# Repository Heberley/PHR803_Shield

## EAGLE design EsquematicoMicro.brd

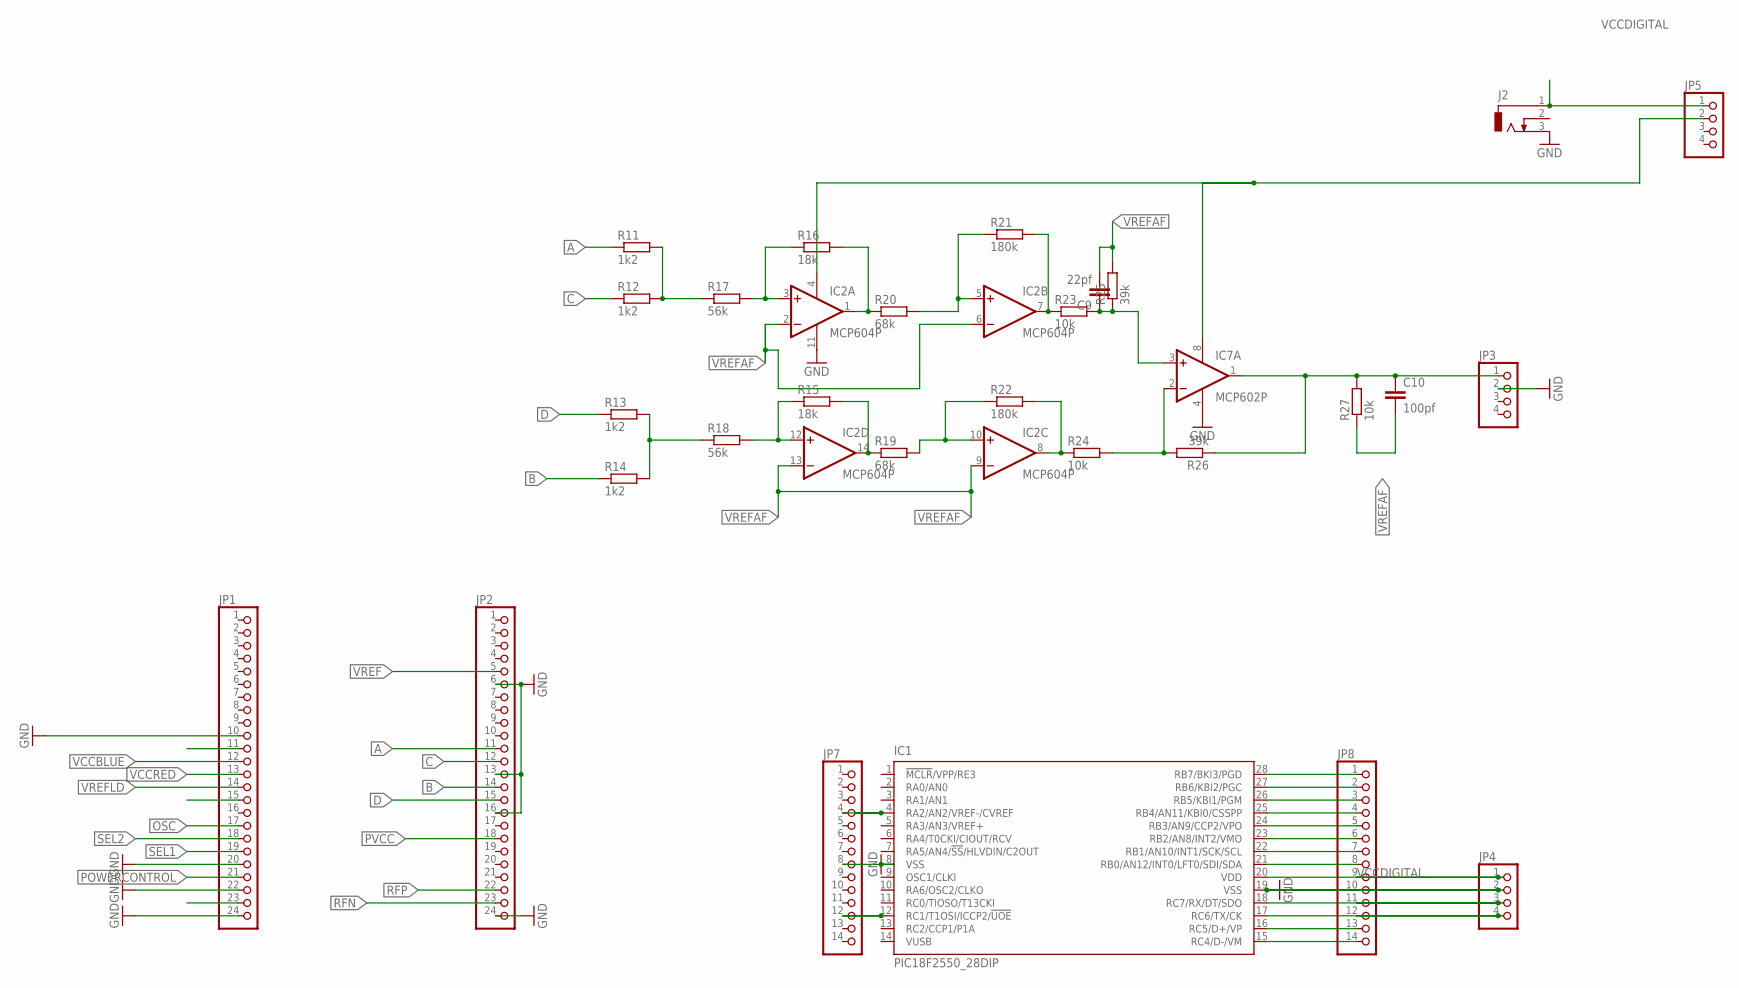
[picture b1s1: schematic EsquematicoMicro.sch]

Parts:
C9: 22pf; C025-025X050
C10: 100pf; C025-025X050
IC1: PIC18F2550_28DIP; DIL28-3
IC2: MCP604P; DIL14
IC7: MCP602P; DIL08
J2: DCJ0303
JP1, JP2: PINHD-1X24; 1X24
JP3, JP4, JP5: PINHD-1X4; 1X04
JP7, JP8: PINHD-1X14; 1X14
R11, R12, R13, R14: 1k2; 0204/5
R15, R16: 18k; 0204/5
R17, R18: 56k; 0204/5
R19, R20: 68k; 0204/5
R21, R22: 180k; 0204/5
R23, R24, R27: 10k; 0204/5
R25, R26: 39k; 0204/5

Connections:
A: JP2.11, R11.1
B: JP2.14, R14.1
C: JP2.12, R12.1
D: JP2.15, R13.1
GND: IC1.8 (VSS), IC1.19 (VSS), IC2.11 (V-), IC7.4 (V-), J2.3, JP1.10, JP1.20, JP1.22, JP1.24, JP2.6, JP2.13, JP2.16, JP2.24, JP3.2, JP4.2, JP7.8, JP8.10
LASERMICRO: IC1.4 (RA2/AN2/VREF-/CVREF), JP7.4
unnamed: IC1.18 (RC7/RX/DT/SDO), JP4.3, JP8.11
unnamed: IC1.17 (RC6/TX/CK), JP4.4, JP8.12
unnamed: IC1.28 (RB7/BKI3/PGD), JP8.1
unnamed: IC1.27 (RB6/KBI2/PGC), JP8.2
unnamed: IC1.25 (RB4/AN11/KBI0/CSSPP), JP8.4
unnamed: IC1.23 (RB2/AN8/INT2/VMO), JP8.6
unnamed: IC1.22 (RB1/AN10/INT1/SCK/SCL), JP8.7
unnamed: IC1.21 (RB0/AN12/INT0/LFT0/SDI/SDA), JP8.8
unnamed: IC1.16 (RC5/D+/VP), JP8.13
unnamed: IC1.15 (RC4/D-/VM), JP8.14
unnamed: IC1.26 (RB5/KBI1/PGM), JP8.3
unnamed: R11.2, R12.2, R17.1
unnamed: R13.2, R14.2, R18.1
unnamed: IC2.3 (+IN), R16.1, R17.2
unnamed: IC2.12 (+IN), R15.1, R18.2
unnamed: IC2.1 (OUT), R16.2, R20.1
unnamed: IC2.14 (OUT), R15.2, R19.1
unnamed: IC2.10 (+IN), R19.2, R22.1
unnamed: IC2.8 (OUT), R22.2, R24.1
unnamed: IC2.5 (+IN), R20.2, R21.1
unnamed: IC2.4 (V+), IC7.8 (V+), JP5.2
unnamed: C9.1, IC7.3 (+IN), R23.2, R25.1
unnamed: IC7.2 (-IN), R24.2, R26.2
unnamed: C10.1, IC7.1 (OUT), JP3.1, R26.1, R27.2
unnamed: IC2.7 (OUT), R21.2, R23.1
OSC: JP1.17
POWERCONTROL: JP1.21
PVCC: JP2.18
PWMTILT: IC1.24 (RB3/AN9/CCP2/VPO), JP8.5
PWMY: IC1.12 (RC1/T1OSI/ICCP2/!UOE), JP7.12
RFN: JP2.23
RFP: JP2.22
SEL1: JP1.19
SEL2: JP1.18
VCCBLUE: JP1.12
VCCDIGITAL: IC1.20 (VDD), J2.1, JP4.1, JP5.1, JP8.9
VCCRED: JP1.13
VREF: JP2.5
VREFAF: C9.2, C10.2, IC2.2 (-IN), IC2.6 (-IN), IC2.9 (-IN), IC2.13 (-IN), R25.2, R27.1
VREFLD: JP1.14

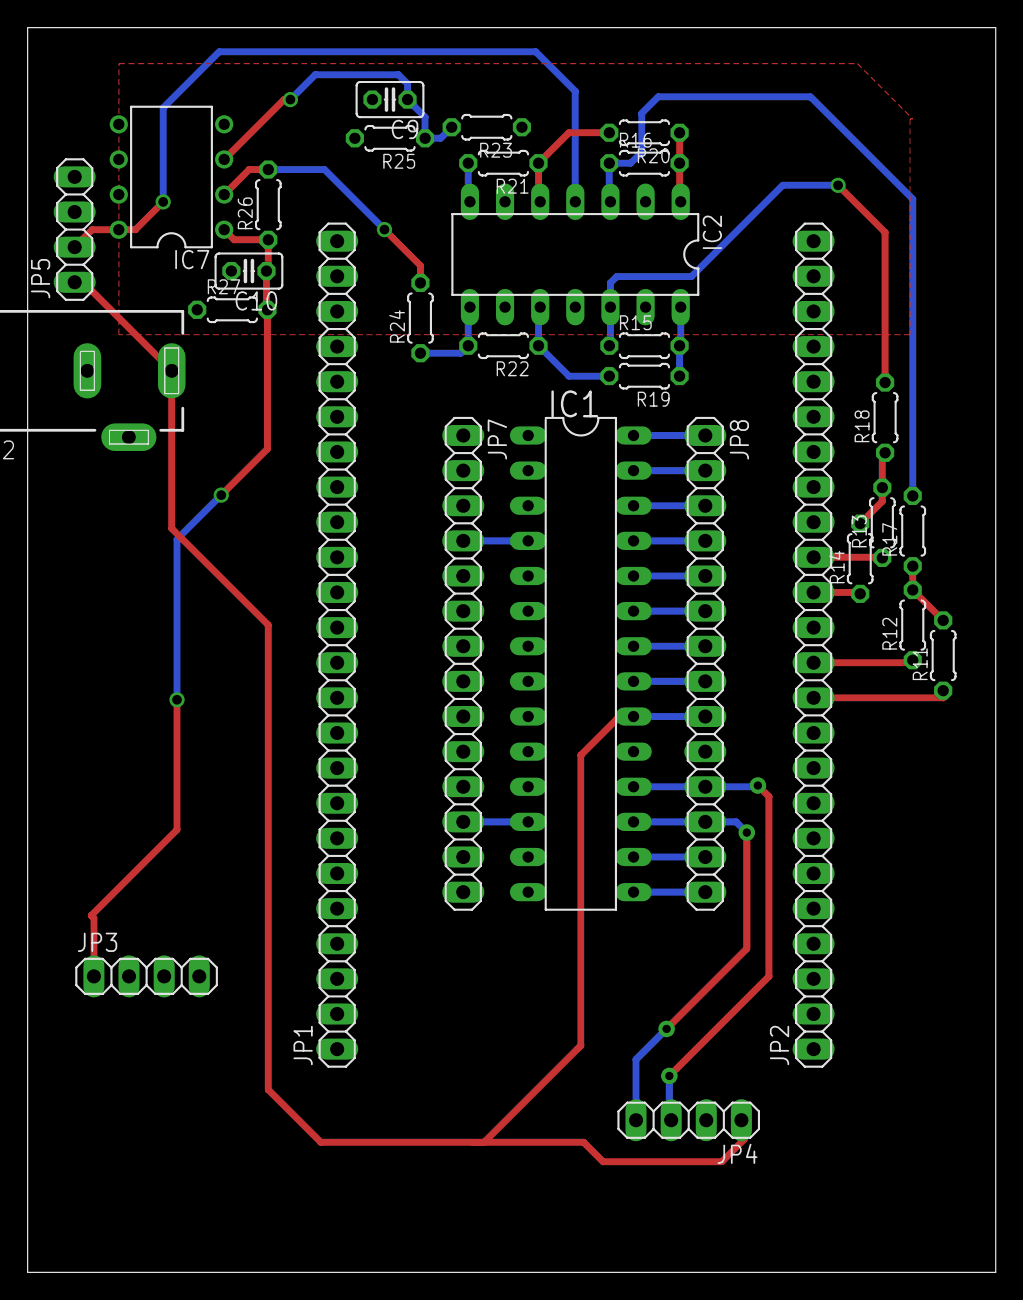
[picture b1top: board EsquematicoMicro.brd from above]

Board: 2 copper layers, 70.0 x 90.0 mm, 30 parts (0 on the bottom side), 35 nets.

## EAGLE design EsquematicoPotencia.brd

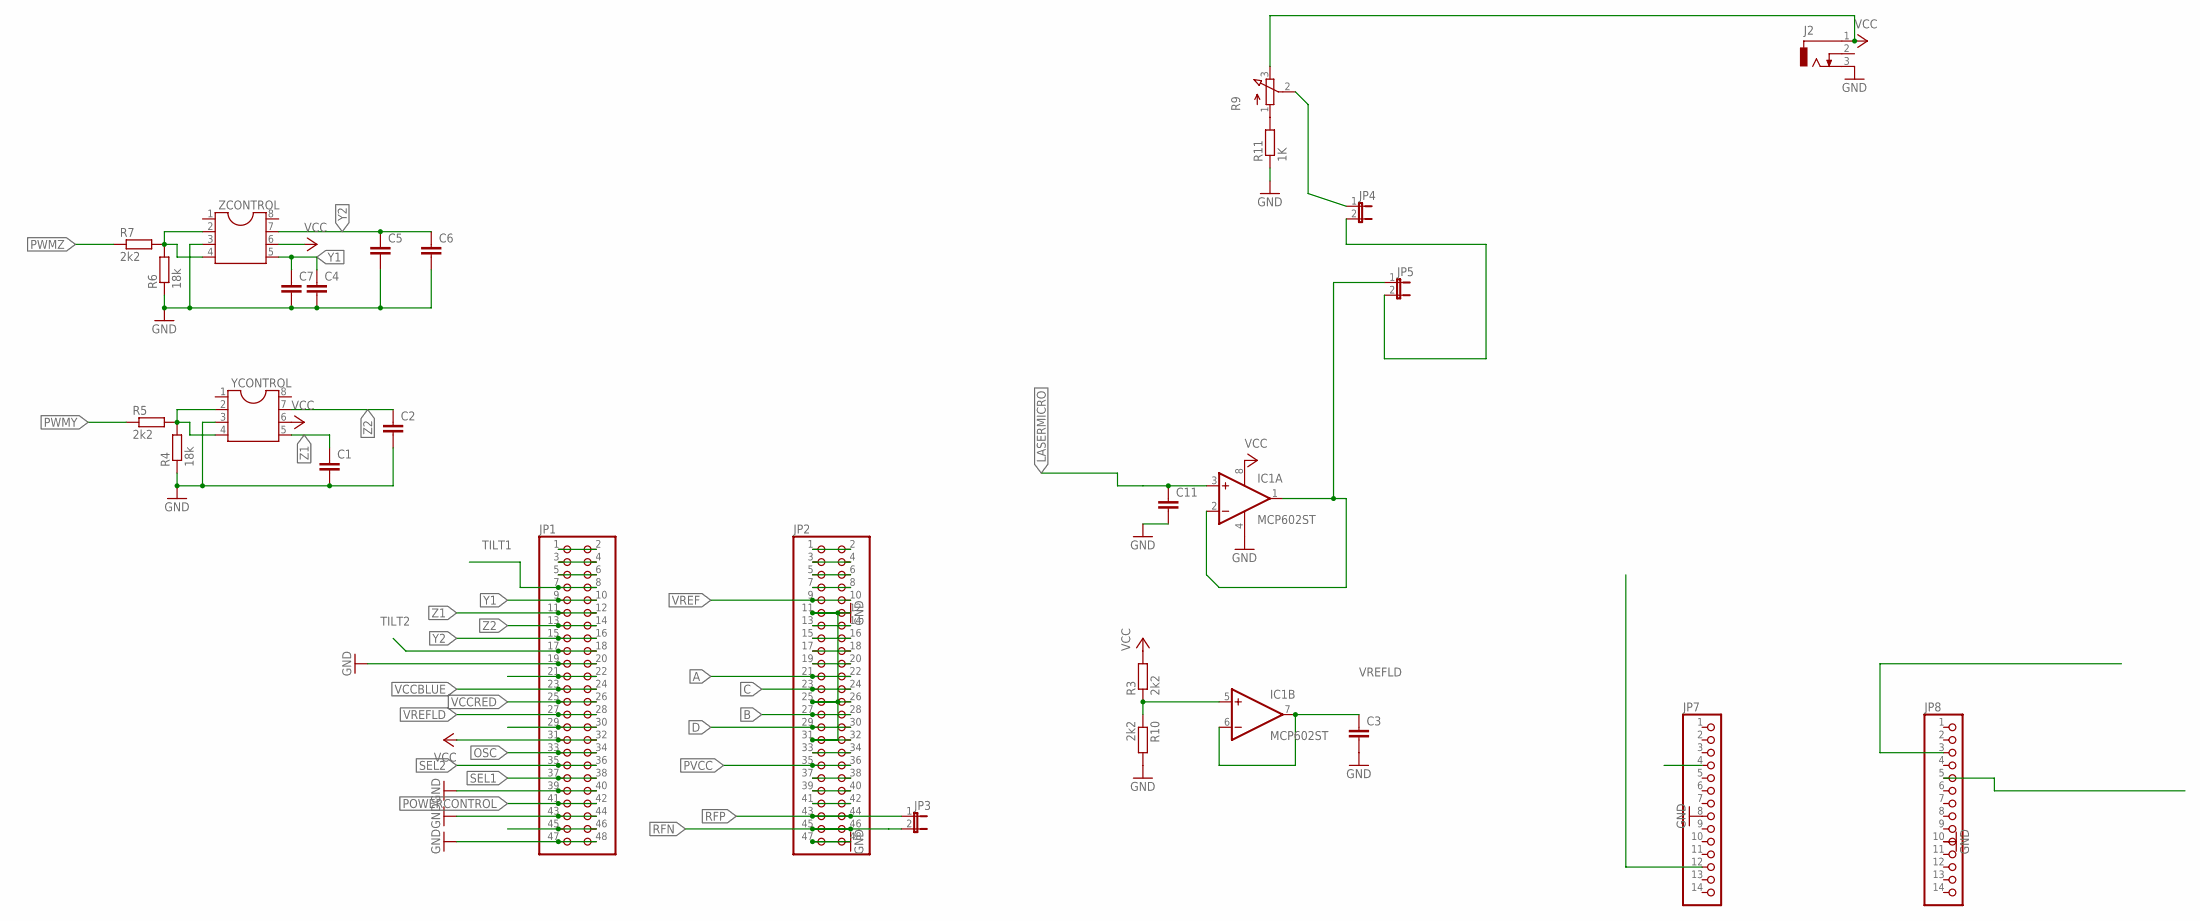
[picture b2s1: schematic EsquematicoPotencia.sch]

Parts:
C1, C2, C3, C4, C5, C6, C7, C11: C-EU025-024X044; C025-024X044
IC1: MCP602ST; TSSOP8
J2: DCJ0303
JP1, JP2: PINHD-2X24; 2X24
JP3, JP4, JP5: JP1E; JP1
JP7, JP8: PINHD-1X14; 1X14
R3, R5, R7, R10: 2k2; 0204/7
R4, R6: 18k; 0204/7
R9: 3RP/1610N
R11: 1K; 0204/7
YCONTROL: DIL8; DIL08
ZCONTROL: DIL8; DIL08

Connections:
A: JP2.21, JP2.22
B: JP2.27, JP2.28
C: JP2.23, JP2.24
D: JP2.29, JP2.30
GND: C1.2, C2.2, C3.2, C4.2, C5.2, C6.2, C7.2, C11.2, IC1.4 (V-), J2.3, JP1.19, JP1.20, JP1.39, JP1.40, JP1.43, JP1.44, JP1.47, JP1.48, JP2.11, JP2.12, JP2.25, JP2.26, JP2.31, JP2.32, JP2.47, JP2.48, JP7.8, JP8.10, R4.1, R6.1, R10.2, R11.1, YCONTROL.3, ZCONTROL.3
LASERMICRO: C11.1, IC1.3 (+IN), JP7.4
unnamed: JP1.21, JP1.22
unnamed: JP1.1, JP1.2
unnamed: R9.1 (A), R11.2
unnamed: R4.2, R5.2, YCONTROL.2, YCONTROL.4
unnamed: R6.2, R7.2, ZCONTROL.2, ZCONTROL.4
unnamed: JP1.29, JP1.30
unnamed: JP1.3, JP1.4
unnamed: IC1.5 (+IN), R3.1, R10.1
unnamed: JP4.1, R9.2 (S)
unnamed: JP1.5, JP1.6
unnamed: IC1.1 (OUT), IC1.2 (-IN), JP5.1
unnamed: JP2.1, JP2.2
unnamed: JP2.3, JP2.4
unnamed: JP1.45, JP1.46
unnamed: JP2.5, JP2.6
unnamed: JP2.7, JP2.8
unnamed: JP2.13, JP2.14
unnamed: JP2.15, JP2.16
unnamed: JP2.17, JP2.18
unnamed: JP2.19, JP2.20
unnamed: JP2.33, JP2.34
unnamed: JP2.37, JP2.38
unnamed: JP2.39, JP2.40
unnamed: JP2.41, JP2.42
OSC: JP1.33, JP1.34
POWERCONTROL: JP1.41, JP1.42, JP4.2, JP5.2
PVCC: JP2.35, JP2.36
PWMTILT: JP8.5
PWMY: JP7.12, R5.1
PWMZ: JP8.3, R7.1
RFN: JP2.45, JP2.46, JP3.2
RFP: JP2.43, JP2.44, JP3.1
SEL1: JP1.37, JP1.38
SEL2: JP1.35, JP1.36
TILT1: JP1.7, JP1.8
TILT2: JP1.17, JP1.18
VCC: IC1.8 (V+), J2.1, JP1.31, JP1.32, R3.2, R9.3 (E), YCONTROL.6, ZCONTROL.6
VCCBLUE: JP1.23, JP1.24
VCCRED: JP1.25, JP1.26
VREF: JP2.9, JP2.10
VREFLD: C3.1, IC1.6 (-IN), IC1.7 (OUT), JP1.27, JP1.28
Y1: C4.1, C7.1, JP1.9, JP1.10, ZCONTROL.5
Y2: C5.1, C6.1, JP1.15, JP1.16, ZCONTROL.7
Z1: C1.1, JP1.11, JP1.12, YCONTROL.5
Z2: C2.1, JP1.13, JP1.14, YCONTROL.7

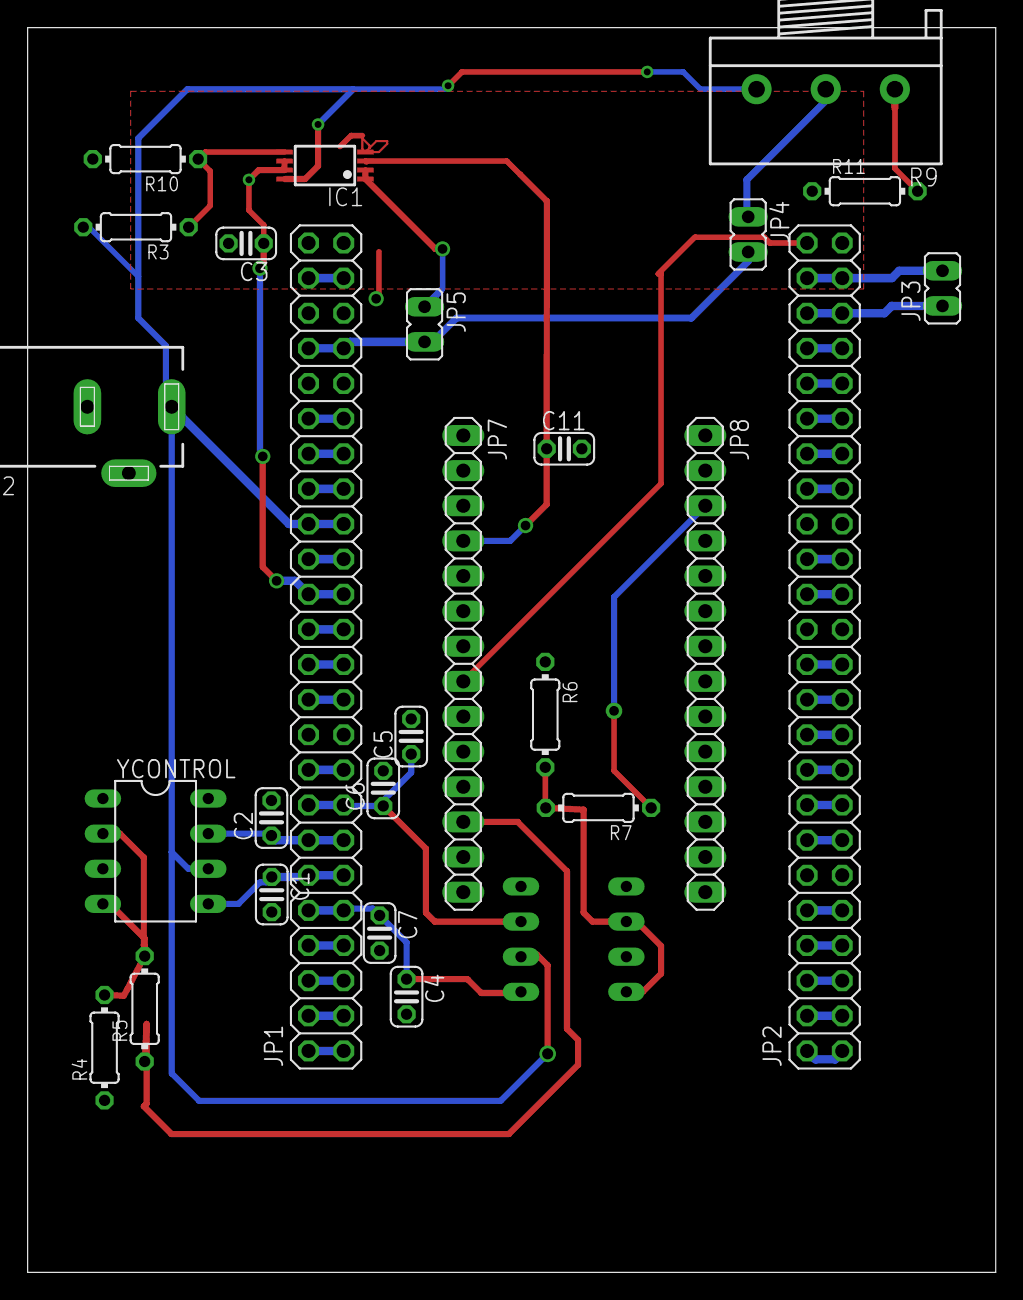
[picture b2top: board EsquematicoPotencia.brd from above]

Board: 2 copper layers, 70.0 x 90.0 mm, 27 parts (1 on the bottom side), 50 nets.
